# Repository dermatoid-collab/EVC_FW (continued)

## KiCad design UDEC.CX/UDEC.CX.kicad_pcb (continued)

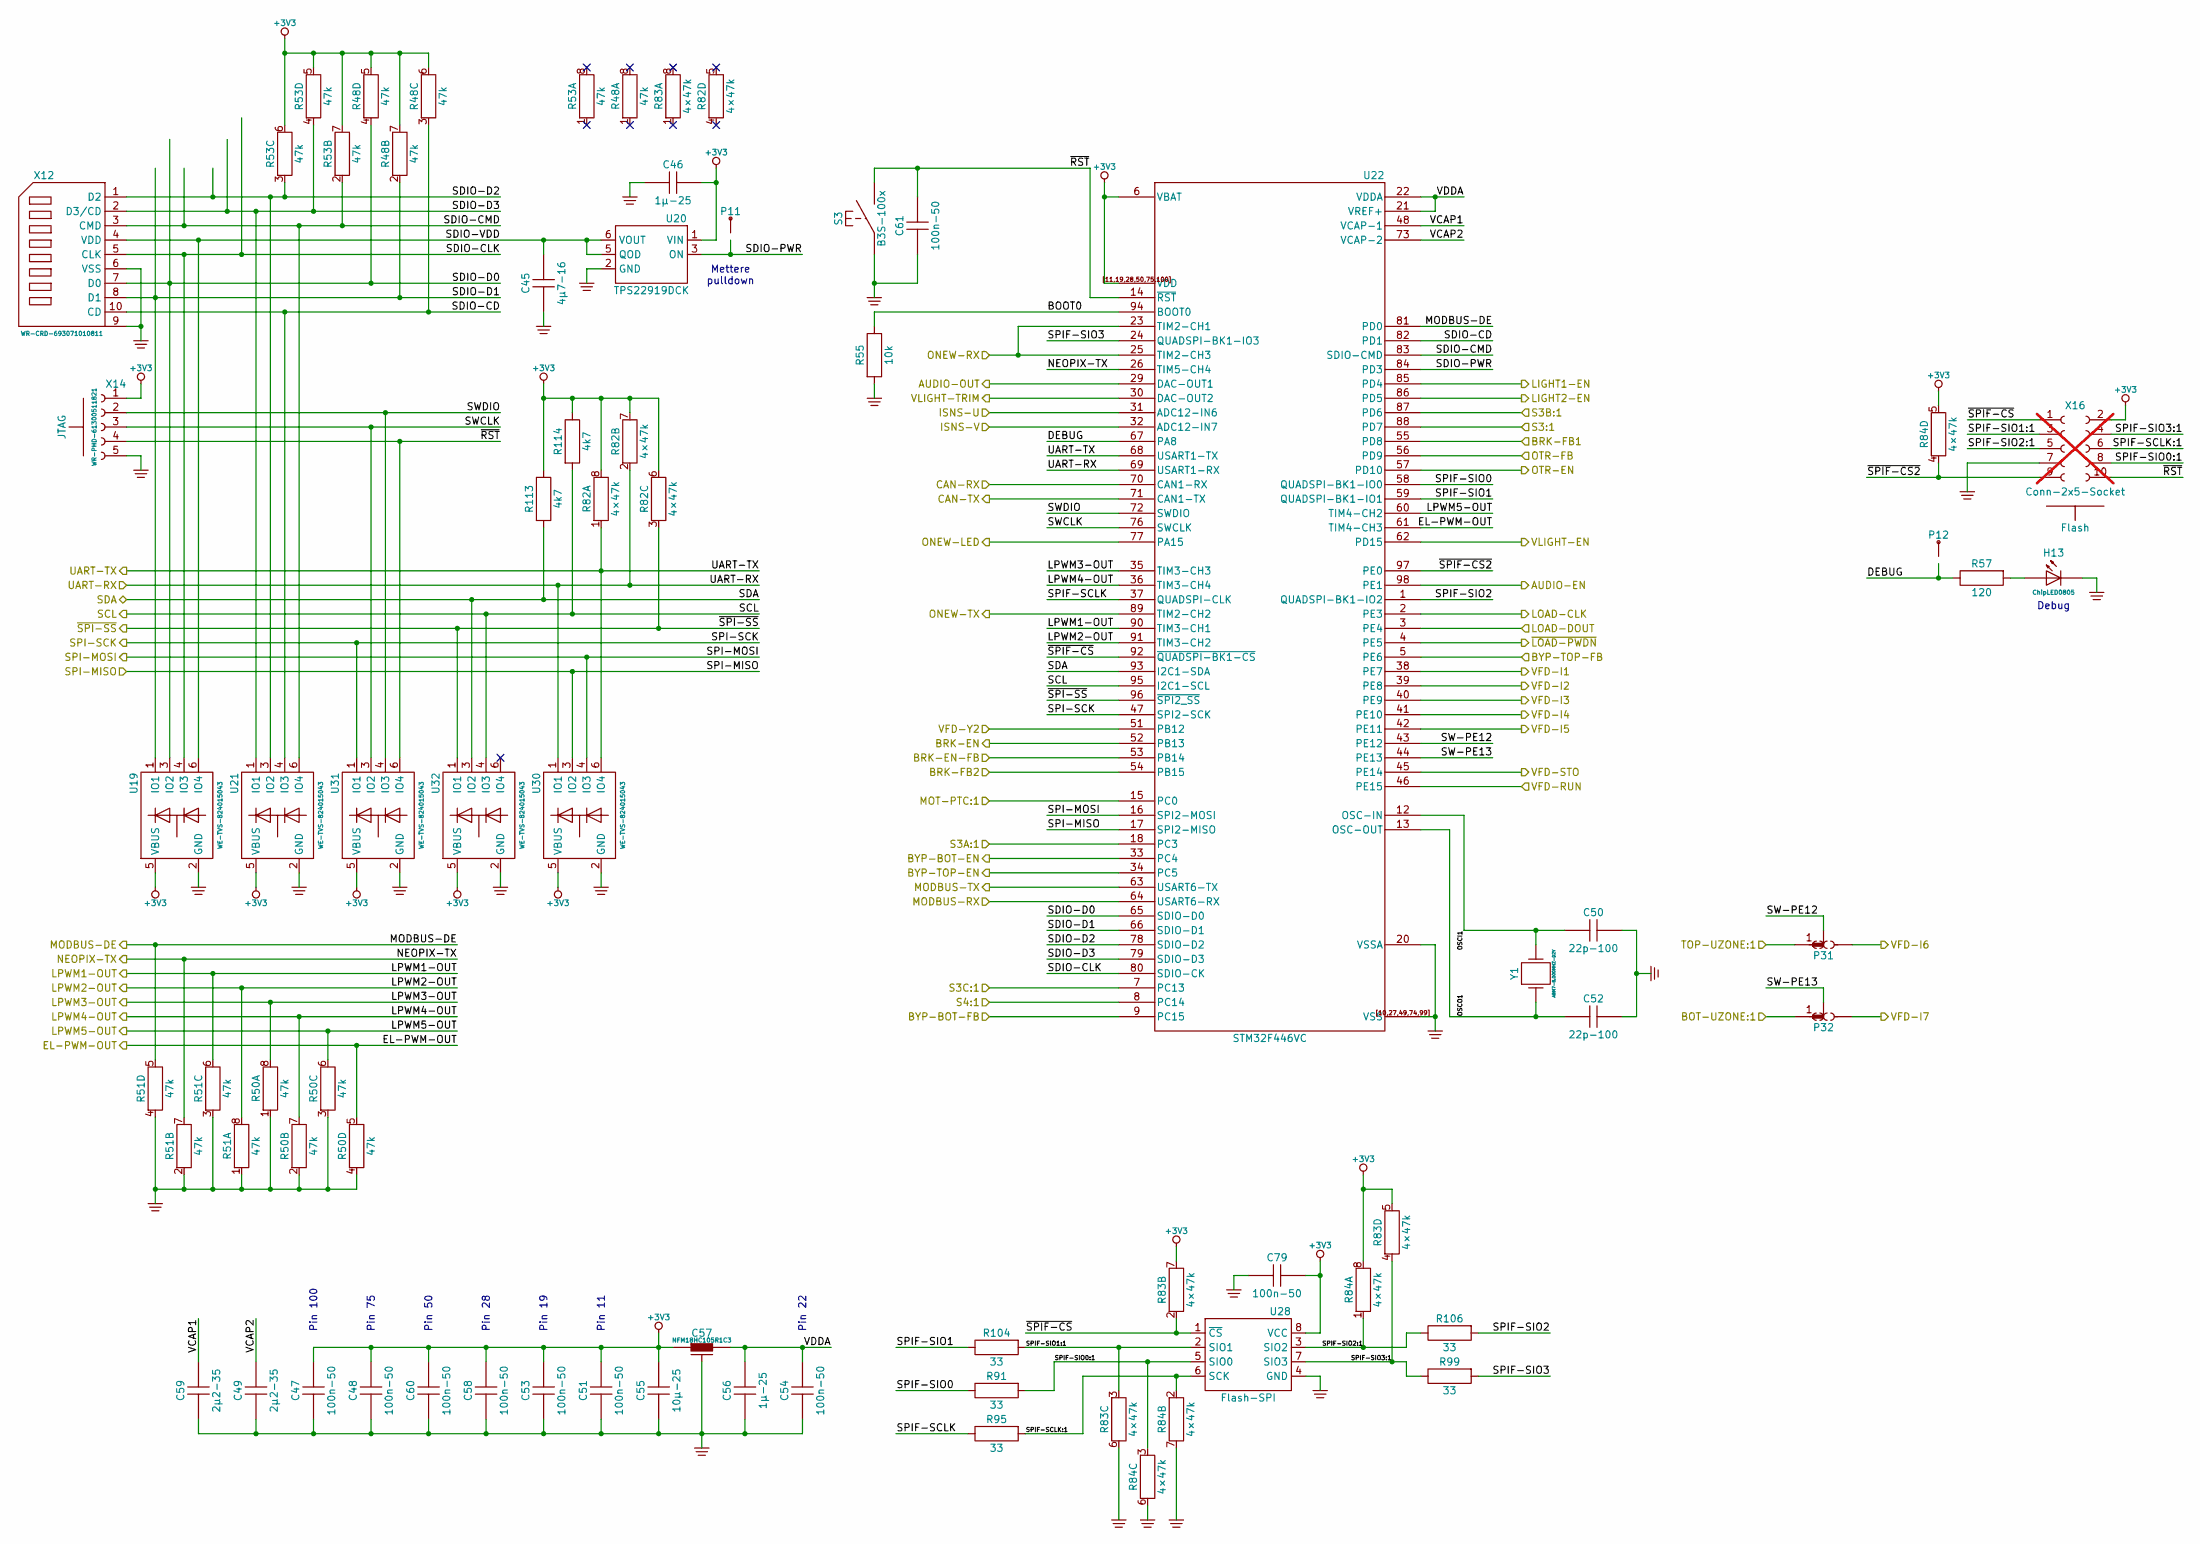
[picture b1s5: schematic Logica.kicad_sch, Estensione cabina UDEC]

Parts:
C45: 4µ7-16; C0603
C46, C56: 1µ-25; C0603
C47, C48, C51, C53, C54, C58, C60, C61, C79: 100n-50; C0603
C49, C59: 2µ2-35; C0603
C50, C52: 22p-100; C0603
C55: 10µ-25; C0805
C57: NFM18HC105R1C3; Murata-NFM18HC105
H13: ChipLED0805; Chipled-0805
P11, P12: PinTst
P31, P32: Solder; Solder-Jumper-CO-Default-03
R48, R50, R51, R53: 47k; KMY-RAC164D
R55: 10k; R0603
R57: 120; R0603
R82, R83, R84: 4×47k; KMY-RAC164D
R91, R95, R99, R104, R106: 33; R0603
R113, R114: 4k7; R0603
S3: B3S-100x; Omron-B3S-100x
U19, U21, U30, U31, U32: WE-TVS-824015043; MO178AB
U20: TPS22919DCK; MO203AB
U22: STM32F446VC; MS026BED
U28: Flash-SPI; MS012AA+208mil
X12: WR-CRD-693071010811
X14: WR-PHD-61300511821; F-5
X16: Conn-2x5-Socket; F-2x5; not fitted
Y1: ABM7-8.000MHZ-D2Y; Abracon-ABM07
ZZZ14: JTAG
ZZZ15: Flash

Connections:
+3V3: C46.2, C47.2, C48.2, C51.2, C53.2, C55.2, C57.1, C58.2, C60.2, C79.2, R48.5, R48.6, R48.7, R53.5, R53.6, R53.7, R82.6, R82.7, R82.8, R83.5, R83.7, R84.5, R84.8, R113.1, R114.1, U19.5 (VBUS), U20.1 (VIN), U21.5 (VBUS), U22.6 (VBAT), U22.11 (VDD), U22.19 (VDD), U22.28 (VDD), U22.50 (VDD), U22.75 (VDD), U22.100 (VDD), U22.[11,19,28,50,75,100] (VDD), U28.8 (VCC), U30.5 (VBUS), U31.5 (VBUS), U32.5 (VBUS), X14.1, X16.2; also elsewhere on the board
/Audio/AUDIO-EN: U22.98 (PE1); also elsewhere on the board
/Audio/AUDIO-OUT: U22.29 (DAC-OUT1); also elsewhere on the board
/Comms/CAN-RX: U22.70 (CAN1-RX); also elsewhere on the board
/Comms/CAN-TX: U22.71 (CAN1-TX); also elsewhere on the board
/Comms/ONEWIRE-LED: U22.77 (PA15); also elsewhere on the board
/Comms/ONEWIRE-RX: U22.23 (TIM2-CH1), U22.25 (TIM2-CH3); also elsewhere on the board
/Comms/ONEWIRE-TX: U22.89 (TIM2-CH2); also elsewhere on the board
/Lighting+EL/BOT-UZONE:1: P32.1 (A); also elsewhere on the board
/Lighting+EL/LIGHT1-EN: U22.85 (PD4); also elsewhere on the board
/Lighting+EL/LIGHT2-EN: U22.86 (PD5); also elsewhere on the board
/Lighting+EL/TOP-UZONE:1: P31.1 (A); also elsewhere on the board
/LoadCell/LOAD-CLK: U22.2 (PE3); also elsewhere on the board
/LoadCell/LOAD-DOUT: U22.3 (PE4); also elsewhere on the board
/LoadCell/~LOAD-PDWN: U22.4 (PE5); also elsewhere on the board
/Logica/BOOT0: R55.1, U22.94 (BOOT0)
/Logica/BRK-EN: U22.52 (PB13); also elsewhere on the board
/Logica/BRK-EN-FB: U22.53 (PB14); also elsewhere on the board
/Logica/BRK-FB1: U22.55 (PD8); also elsewhere on the board
/Logica/BRK-FB2: U22.54 (PB15); also elsewhere on the board
/Logica/BYP-BOT-EN: U22.33 (PC4); also elsewhere on the board
/Logica/BYP-BOT-FB: U22.9 (PC15); also elsewhere on the board
/Logica/BYP-TOP-EN: U22.34 (PC5); also elsewhere on the board
/Logica/BYP-TOP-FB: U22.5 (PE6); also elsewhere on the board
/Logica/DEBUG: P12.1, R57.1, U22.67 (PA8)
/Logica/EL-PWM-OUT: R50.5, U22.61 (TIM4-CH3); also elsewhere on the board
/Logica/ISNS-U: U22.31 (ADC12-IN6); also elsewhere on the board
/Logica/ISNS-V: U22.32 (ADC12-IN7); also elsewhere on the board
/Logica/LPWM1-OUT: R51.6, U22.90 (TIM3-CH1); also elsewhere on the board
/Logica/LPWM2-OUT: R51.8, U22.91 (TIM3-CH2); also elsewhere on the board
/Logica/LPWM3-OUT: R50.8, U22.35 (TIM3-CH3); also elsewhere on the board
/Logica/LPWM4-OUT: R50.7, U22.36 (TIM3-CH4); also elsewhere on the board
/Logica/LPWM5-OUT: R50.6, U22.60 (TIM4-CH2); also elsewhere on the board
/Logica/MODBUS-DE: R51.5, U22.81 (PD0); also elsewhere on the board
/Logica/MODBUS-RX: U22.64 (USART6-RX); also elsewhere on the board
/Logica/MODBUS-TX: U22.63 (USART6-TX); also elsewhere on the board
/Logica/MOT-PTC:1: U22.15 (PC0); also elsewhere on the board
/Logica/NEOPIX-TX: R51.7, U22.26 (TIM5-CH4); also elsewhere on the board
/Logica/OSCI1: C50.2, U22.12 (OSC-IN), Y1.2
/Logica/OSCO1: C52.2, U22.13 (OSC-OUT), Y1.1
/Logica/OTR-EN: U22.57 (PD10); also elsewhere on the board
/Logica/OTR-FB: U22.56 (PD9); also elsewhere on the board
/Logica/S3:1: U22.88 (PD7); also elsewhere on the board
/Logica/S3A:1: U22.18 (PC3); also elsewhere on the board
/Logica/S3B:1: U22.87 (PD6); also elsewhere on the board
/Logica/S3C:1: U22.7 (PC13); also elsewhere on the board
/Logica/S4:1: U22.8 (PC14); also elsewhere on the board
/Logica/SDIO-CD: R48.3, U21.4 (IO3), U22.82 (PD1), X12.10 (CD)
/Logica/SDIO-CLK: U19.4 (IO3), U22.80 (SDIO-CK), X12.5 (CLK)
/Logica/SDIO-CMD: R53.2, U21.6 (IO4), U22.83 (SDIO-CMD), X12.3 (CMD)
/Logica/SDIO-D0: R48.4, U19.3 (IO2), U22.65 (SDIO-D0), X12.7 (D0)
/Logica/SDIO-D1: R48.2, U19.1 (IO1), U22.66 (SDIO-D1), X12.8 (D1)
/Logica/SDIO-D2: R53.3, U21.3 (IO2), U22.78 (SDIO-D2), X12.1 (D2)
/Logica/SDIO-D3: R53.4, U21.1 (IO1), U22.79 (SDIO-D3), X12.2 (D3/CD)
/Logica/SDIO-PWR: P11.1, U20.3 (ON), U22.84 (PD3)
/Logica/SDIO-VDD: C45.2, U19.6 (IO4), U20.5 (QOD), U20.6 (VOUT), X12.4 (VDD)
/Logica/SPIF-SCLK: R95.1, U22.37 (QUADSPI-CLK)
/Logica/SPIF-SCLK:1: R84.2, R95.2, U28.6 (SCK), X16.6
/Logica/SPIF-SIO0: R91.1, U22.58 (QUADSPI-BK1-IO0)
/Logica/SPIF-SIO0:1: R84.3, R91.2, U28.5 (SIO0), X16.8
/Logica/SPIF-SIO1: R104.1, U22.59 (QUADSPI-BK1-IO1)
/Logica/SPIF-SIO1:1: R83.3, R104.2, U28.2 (SIO1), X16.3
/Logica/SPIF-SIO2: R106.2, U22.1 (QUADSPI-BK1-IO2)
/Logica/SPIF-SIO2:1: R84.1, R106.1, U28.3 (SIO2), X16.5
/Logica/SPIF-SIO3: R99.2, U22.24 (QUADSPI-BK1-IO3)
/Logica/SPIF-SIO3:1: R83.4, R99.1, U28.7 (SIO3), X16.4
/Logica/SW-PE12: P31.2 (C), U22.43 (PE12)
/Logica/SW-PE13: P32.2 (C), U22.44 (PE13)
/Logica/SWCLK: U22.76 (SWCLK), U31.3 (IO2), X14.3
/Logica/SWDIO: U22.72 (SWDIO), U31.4 (IO3), X14.2
/Logica/VCAP1: C59.2, U22.48 (VCAP-1)
/Logica/VCAP2: C49.2, U22.73 (VCAP-2)
/Logica/VDDA: C54.2, C56.2, C57.2, U22.21 (VREF+), U22.22 (VDDA)
/Logica/VFD-I1: U22.38 (PE7); also elsewhere on the board
/Logica/VFD-I2: U22.39 (PE8); also elsewhere on the board
/Logica/VFD-I3: U22.40 (PE9); also elsewhere on the board
/Logica/VFD-I4: U22.41 (PE10); also elsewhere on the board
/Logica/VFD-I5: U22.42 (PE11); also elsewhere on the board
/Logica/VFD-I6: P31.3 (B); also elsewhere on the board
/Logica/VFD-I7: P32.3 (B); also elsewhere on the board
/Logica/VFD-RUN: U22.46 (PE15); also elsewhere on the board
/Logica/VFD-STO: U22.45 (PE14); also elsewhere on the board
/Logica/VFD-Y2: U22.51 (PB12); also elsewhere on the board
/Logica/VLIGHT-EN: U22.62 (PD15); also elsewhere on the board
/Logica/VLIGHT-TRIM: U22.30 (DAC-OUT2); also elsewhere on the board
/Logica/~RST: C61.2, S3.14, S3.14A, S3.14B (14A), U22.14 (~RST), U31.6 (IO4), X14.4, X16.10
/Logica/~SPIF-CS2: R84.4, U22.97 (PE0), X16.9
/Logica/~SPIF-CS: R83.2, U22.92 (~QUADSPI-BK1-CS), U28.1 (~CS), X16.1
/SCL: R114.2, U22.95 (I2C1-SCL), U32.4 (IO3); also elsewhere on the board
/SDA: R113.2, U22.93 (I2C1-SDA), U32.3 (IO2); also elsewhere on the board
/SPI-MISO: U22.17 (SPI2-MISO), U30.3 (IO2); also elsewhere on the board
/SPI-MOSI: U22.16 (SPI2-MOSI), U30.4 (IO3); also elsewhere on the board
/SPI-SCK: U22.47 (SPI2-SCK), U31.1 (IO1); also elsewhere on the board
/UART-RX: R82.2, U22.69 (USART1-RX), U30.1 (IO1); also elsewhere on the board
/UART-TX: R82.1, U22.68 (USART1-TX), U30.6 (IO4); also elsewhere on the board
/~SPI-SS: R82.3, U22.96 (~SPI2_SS), U32.1 (IO1); also elsewhere on the board
GND: C45.1, C46.1, C47.1, C48.1, C49.1, C50.1, C51.1, C52.1, C53.1, C54.1, C55.1, C56.1, C57.3, C58.1, C59.1, C60.1, C61.1, C79.1, H13.K, R50.1, R50.2, R50.3, R50.4, R51.1, R51.2, R51.3, R51.4, R55.2, R83.6, R84.6, R84.7, S3.13, S3.13A, S3.13B, U19.2 (GND), U20.2 (GND), U21.2 (GND), U22.10 (VSS), U22.20 (VSSA), U22.27 (VSS), U22.49 (VSS), U22.74 (VSS), U22.99 (VSS), U22.[10,27,49,74,99] (VSS), U28.4 (GND), U30.2 (GND), U31.2 (GND), U32.2 (GND), X12.6 (VSS), X12.9, X14.5, X16.7; also elsewhere on the board
unnamed: H13.A, R57.2

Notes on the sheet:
Pin 50
Pin 28
Pin 19
Pin 22
Mettere pulldown
Debug
Pin 100
Pin 11
Pin 75

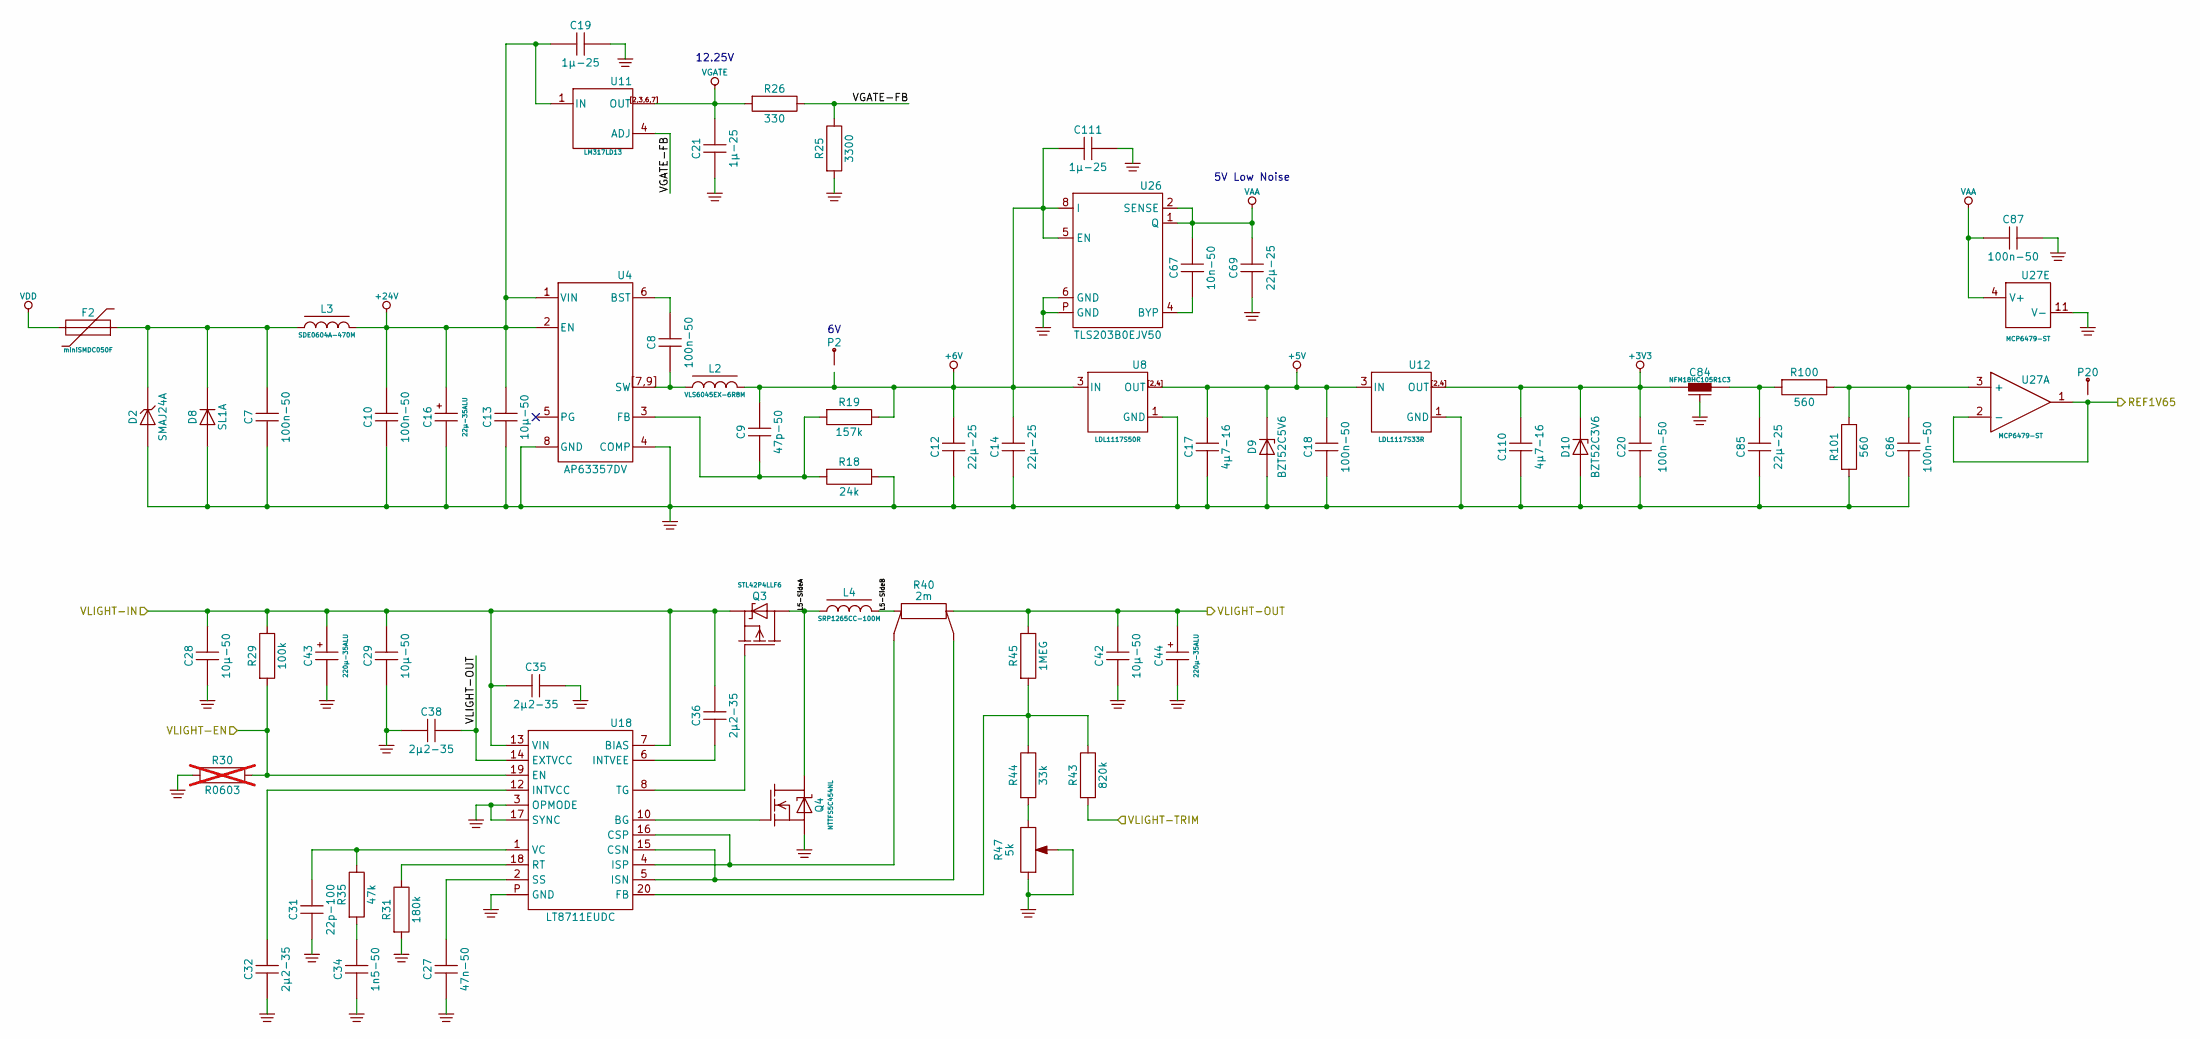
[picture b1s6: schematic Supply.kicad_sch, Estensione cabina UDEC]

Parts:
C7, C8, C10, C18, C20, C86, C87: 100n-50; C0603
C9: 47p-50; C0603
C12, C14, C69, C85: 22µ-25; C0805
C13, C28, C29, C42: 10µ-50; C1206
C16: 22µ-35ALU; CPV-5x5.5
C17, C110: 4µ7-16; C0603
C19, C21, C111: 1µ-25; C0603
C27: 47n-50; C0603
C31: 22p-100; C0603
C32, C35, C36, C38: 2µ2-35; C0603
C34: 1n5-50; C0603
C43, C44: 220µ-35ALU; CPV-8x10.5
C67: 10n-50; C0603
C84: NFM18HC105R1C3; Murata-NFM18HC105
D2: SMAJ24A; DO214AC
D8: SL1A; SOD123FL
D9: BZT52C5V6; SOD123
D10: BZT52C3V6; SOD123
F2: miniSMDC050F; miniSMDC
L2: VLS6045EX-6R8M; TDK-VLS6045EX
L3: SDE0604A-470M; Bourns-SDE0604A
L4: SRP1265CC-100M; Bourns-SRP1265CC
P2, P20: PinTst
Q3: STL42P4LLF6; ST-PowerFlat-5x6-R-SUBCON-SSSGDDDD
Q4: NTTFS5C454NL; Onsemi-WDFN8-511AB
R18: 24k; R0603
R19: 157k; R0603
R25: 3300; R0603
R26: 330; R0603
R29: 100k; R0603
R30: R0603; not fitted
R31: 180k; R0603
R35: 47k; R0603
R40: 2m; R2512K
R43: 820k; R0603
R44: 33k; R0603
R45: 1MEG; R0603
R47: 5k; Vishay-T73YP
R100, R101: 560; R0603
U4: AP63357DV; Diodes-V-DFN3020-13A
U8: LDL1117S50R; TO261AA
U11: LM317LD13; MS012AA
U12: LDL1117S33R; TO261AA
U18: LT8711EUDC; Linear-UDC20
U26: TLS203B0EJV50; MS012BA
U27: MCP6479-ST; MO153AB1

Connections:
+3V3: C20.2, C84.1, C110.2, D10.K, U12.2 (OUT), U12.4 (OUT), U12.[2,4] (OUT); also elsewhere on the board
+5V: C17.2, C18.2, D9.K, U8.2 (OUT), U8.4 (OUT), U8.[2,4] (OUT), U12.3 (IN); also elsewhere on the board
+6V: C9.2, C12.2, C14.2, C111.2, L2.2, P2.1, R19.1, U8.3 (IN), U26.5 (EN), U26.8 (I); also elsewhere on the board
+24V: C10.2, C13.2, C16.+, C19.1, L3.2, U4.1 (VIN), U4.2 (EN), U11.1 (IN); also elsewhere on the board
/Logica/VLIGHT-EN: R29.2, R30.1, U18.19 (EN); also elsewhere on the board
/Logica/VLIGHT-TRIM: R43.2; also elsewhere on the board
/REF1V65: P20.1, U27.1, U27.2 (-); also elsewhere on the board
/Supply/L5-SideA: L4.1, Q3.D, Q4.D
/Supply/L5-SideB: L4.2, R40.2
/Supply/VGATE-FB: R25.1, R26.1, U11.4 (ADJ)
/VLIGHT-IN: C28.2, C29.2, C35.1, C36.2, C43.+, Q3.S, R29.1, U18.7 (BIAS), U18.13 (VIN); also elsewhere on the board
/VLIGHT-OUT: C38.2, C42.2, C44.+, R40.1, R45.1, U18.14 (EXTVCC); also elsewhere on the board
GND: C7.1, C10.1, C12.1, C13.1, C14.1, C16.-, C17.1, C18.1, C19.2, C20.1, C21.1, C27.1, C28.1, C29.1, C31.1, C32.1, C34.1, C35.2, C38.1, C42.1, C43.-, C44.-, C69.1, C84.3, C85.1, C86.1, C87.2, C110.1, C111.1, D2.A, D8.A, D9.A, D10.A, Q4.S, R18.1, R25.2, R30.2, R31.2, R47.3, R47.W, R101.2, U4.4 (COMP), U4.8 (GND), U8.1 (GND), U12.1 (GND), U18.3 (OPMODE), U18.17 (SYNC), U18.P (GND), U26.6 (GND), U26.P (GND), U27.11 (V-); also elsewhere on the board
unnamed: C7.2, D2.K, D8.K, F2.2, L3.1
unnamed: C34.2, R35.2
unnamed: C84.2, C85.2, R100.2
unnamed: R44.2, R47.1
unnamed: C8.2, U4.6 (BST)
unnamed: C9.1, R18.2, R19.2, U4.3 (FB)
unnamed: C8.1, L2.1, U4.7 (SW), U4.9 (SW), U4.[7,9] (SW)
unnamed: Q4.G, U18.10 (BG)
unnamed: R40.3, U18.5 (ISN), U18.15 (CSN)
unnamed: R40.4, U18.4 (ISP), U18.16 (CSP)
unnamed: R43.1, R44.1, R45.2, U18.20 (FB)
unnamed: C32.2, U18.12 (INTVCC)
unnamed: C36.1, U18.6 (INTVEE)
unnamed: R31.1, U18.18 (RT)
unnamed: C27.2, U18.2 (SS)
unnamed: Q3.G, U18.8 (TG)
unnamed: C31.2, R35.1, U18.1 (VC)
unnamed: C67.1, U26.4 (BYP)
unnamed: C86.2, R100.1, R101.1, U27.3 (+)
VAA: C67.2, C69.2, C87.1, U26.1 (Q), U26.2 (SENSE), U27.4 (V+); also elsewhere on the board
VDD: F2.1; also elsewhere on the board
VGATE: C21.2, R26.2, U11.2 (OUT), U11.3 (OUT), U11.6 (OUT), U11.7 (OUT), U11.[2,3,6,7] (OUT); also elsewhere on the board

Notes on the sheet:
5V Low Noise
12.25V

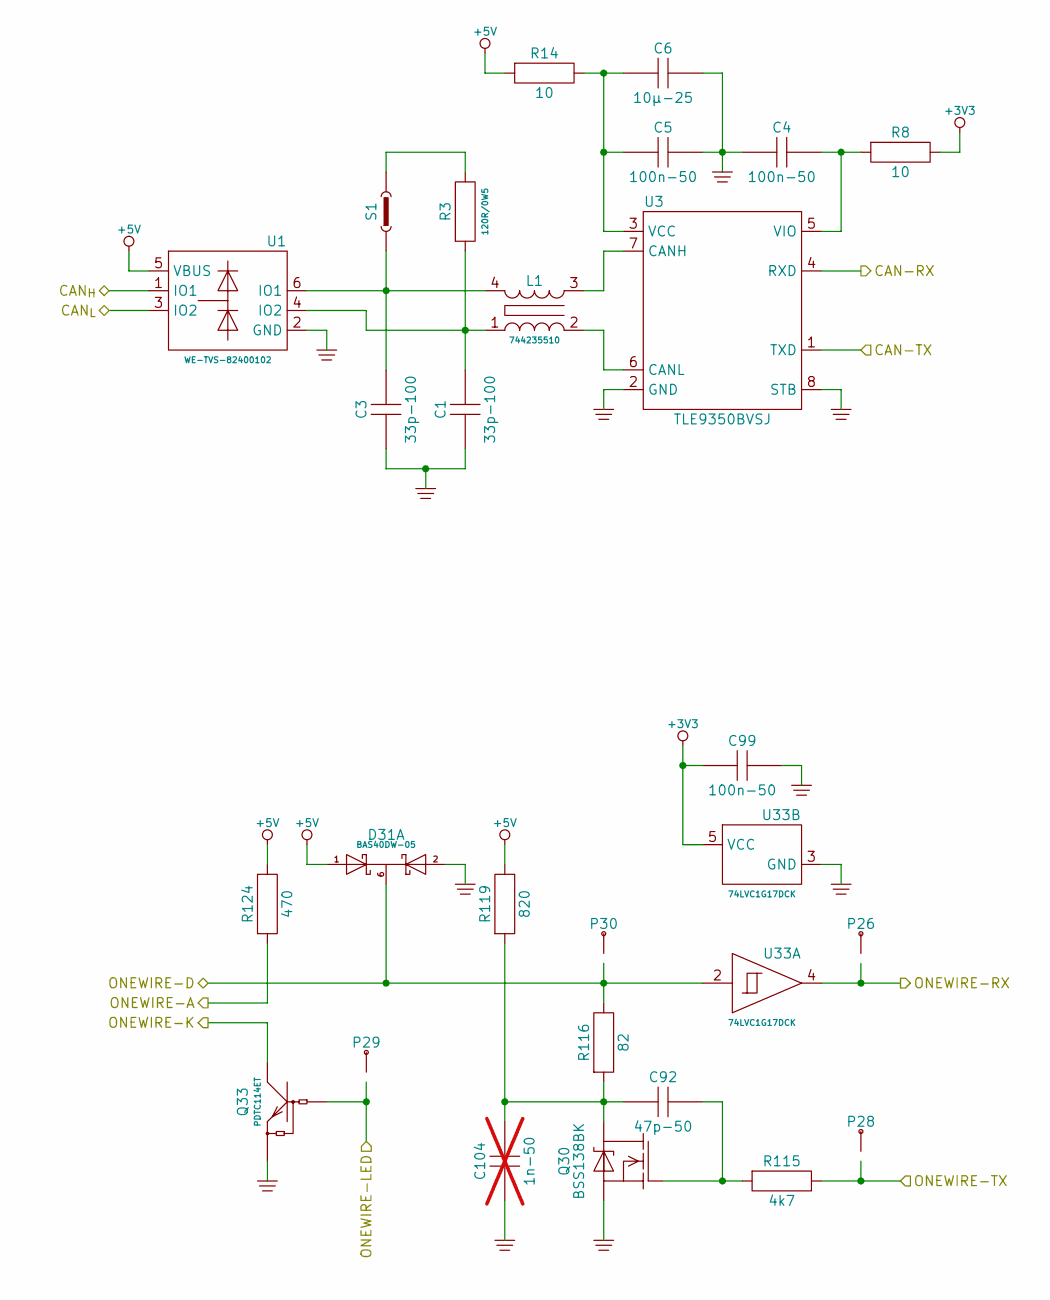
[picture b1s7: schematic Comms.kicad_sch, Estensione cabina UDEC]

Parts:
C1, C3: 33p-100; C0603
C4, C5, C99: 100n-50; C0603
C6: 10µ-25; C0805
C92: 47p-50; C0603
C104: 1n-50; C0603; not fitted
D31: BAS40DW-05; MO203AB
L1: 744235510; WE-CNSW-1812
P26, P28, P29, P30: PinTst
Q30: BSS138BK; TO236-GSD
Q33: PDTC114ET; TO236-BEC
R3: 120R/0W5; R1210
R8, R14: 10; R0603
R115: 4k7; R0603
R116: 82; R0603
R119: 820; R0603
R124: 470; R0603
S1: Jumper-2.54
U1: WE-TVS-82400102; MO178AB
U3: TLE9350BVSJ; MS012AA
U33: 74LVC1G17DCK; MO203AA

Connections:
+3V3: C99.2, R8.1, U33.5 (VCC); also elsewhere on the board
+5V: D31.1 (A1), R14.2, R119.1, R124.1, U1.5 (VBUS); also elsewhere on the board
/CAN_{H}: U1.1 (IO1); also elsewhere on the board
/CAN_{L}: U1.3 (IO2); also elsewhere on the board
/Comms/CAN-RX: U3.4 (RXD); also elsewhere on the board
/Comms/CAN-TX: U3.1 (TXD); also elsewhere on the board
/Comms/ONEWIRE-LED: P29.1, Q33.B; also elsewhere on the board
/Comms/ONEWIRE-RX: P26.1, U33.4; also elsewhere on the board
/Comms/ONEWIRE-TX: P28.1, R115.1; also elsewhere on the board
/ONEWIRE-A: R124.2; also elsewhere on the board
/ONEWIRE-D: D31.6 (K), P30.1, R116.1, U33.2; also elsewhere on the board
/ONEWIRE-K: Q33.C; also elsewhere on the board
GND: C1.1, C3.1, C4.2, C5.1, C6.2, C99.1, C104.1, D31.2 (A2), Q30.S, Q33.E, U1.2 (GND), U3.2 (GND), U3.8 (STB), U33.3 (GND); also elsewhere on the board
unnamed: C1.2, L1.1, R3.2, U1.4 (IO2)
unnamed: C3.2, L1.4, S1.1, U1.6 (IO1)
unnamed: C92.2, Q30.G, R115.2
unnamed: C92.1, C104.2, Q30.D, R116.2, R119.2
unnamed: R3.1, S1.2
unnamed: L1.3, U3.7 (CANH)
unnamed: L1.2, U3.6 (CANL)
unnamed: C5.2, C6.1, R14.1, U3.3 (VCC)
unnamed: C4.1, R8.2, U3.5 (VIO)

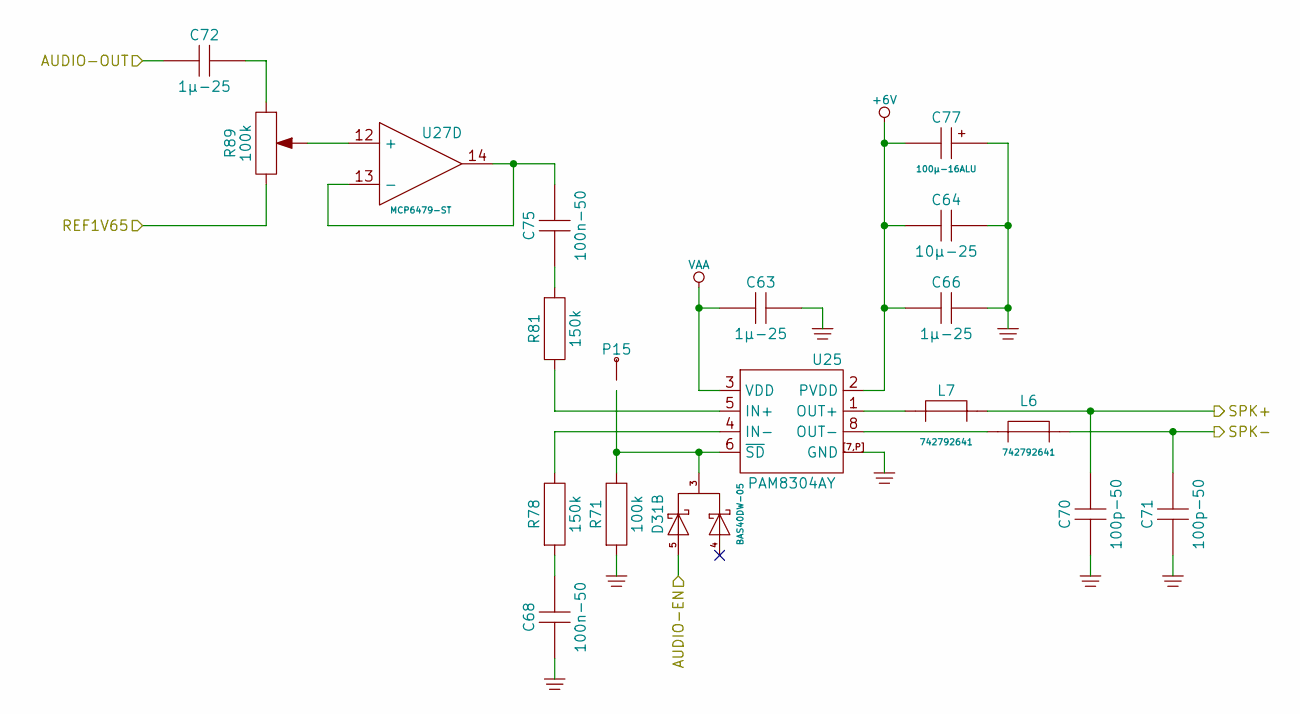
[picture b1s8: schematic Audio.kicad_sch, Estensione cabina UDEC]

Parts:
C63, C66, C72: 1µ-25; C0603
C64: 10µ-25; C0805
C68, C75: 100n-50; C0603
C70, C71: 100p-50; C0603
C77: 100µ-16ALU; CPV-6.3x5.5
D31: BAS40DW-05; MO203AB
L6, L7: 742792641; WE-CBF-0603-HC
P15: PinTst
R71: 100k; R0603
R78, R81: 150k; R0603
R89: 100k; Vishay-T73YP
U25: PAM8304AY; Diodes-U-DFN3030-8-E
U27: MCP6479-ST; MO153AB1

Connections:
+6V: C64.1, C66.1, C77.-, U25.2 (PVDD); also elsewhere on the board
/Audio/AUDIO-EN: D31.5 (A2); also elsewhere on the board
/Audio/AUDIO-OUT: C72.1; also elsewhere on the board
/REF1V65: R89.1; also elsewhere on the board
/SPK+: C70.2, L7.2; also elsewhere on the board
/SPK-: C71.2, L6.2; also elsewhere on the board
GND: C63.2, C64.2, C66.2, C68.1, C70.1, C71.1, C77.+, R71.2, U25.7 (GND), U25.P (GND), U25.[7,P] (GND); also elsewhere on the board
unnamed: C68.2, R78.2
unnamed: C72.2, R89.3
unnamed: C75.2, R81.2
unnamed: D31.3 (K), P15.1, R71.1, U25.6 (~SD)
unnamed: R81.1, U25.5 (IN+)
unnamed: R78.1, U25.4 (IN-)
unnamed: L7.1, U25.1 (OUT+)
unnamed: L6.1, U25.8 (OUT-)
unnamed: R89.W, U27.12 (+)
unnamed: C75.1, U27.13 (-), U27.14
VAA: C63.1, U25.3 (VDD); also elsewhere on the board

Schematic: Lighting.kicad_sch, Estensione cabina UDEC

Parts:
C2, C39, C40, C41: 100n-50; C0603
C24, C25, C26: 1µ-25; C0603
C107, C108: 10n-50; C0603
C109: 1µ-50; C1206
D11: BAS40DW-06; MO203AB
D12: BAS40DW-05; MO203AB
D14, D15, D16, D17, D18: SMAJ24A; DO214AC; not fitted
D19, D32, D37: SMAJ24A; DO214AC
D33, D34: MBRS240; DO214AA
H14, H21, H27, H28: ChipLED0805; Chipled-0805
K6, K7: G5LE-1DC24; Omron-G5LE-1
P24, P25: PinTst
Q5, Q6, Q7, Q8, Q9, Q10: NTTFS5C454NL; Onsemi-WDFN8-511AB
Q31: NUD3160D; MO193AA
R42: 330; R0603
R46, R49, R52, R54, R56, R58: 4R7; R0603
R73, R107: 3.3k/0W25; R1206
R127, R128: WE-VS-82550250; WE-VS-0805
R129, R130: 1k8 250mW; R1206
R131, R132: 270; R0603
R133: 68k; R0603
R134: 1k5; R0603
U2: 74AHCT1G125GV; MO178AA
U15, U16, U17: 2EDN7534BXTSA1; MO178AB
U34: MAX15162ATG; MO220WGGD2

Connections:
+3V3: D12.3 (K), U34.1 (EN2), U34.24 (EN1); also elsewhere on the board
+5V: C2.1, U2.5 (VCC); also elsewhere on the board
+24V: K6.A1, K7.A1, R73.1, R107.1; also elsewhere on the board
/BOT-UZONE: D33.A, R128.2, R130.2; also elsewhere on the board
/EL_{M}: D19.K, Q10.D; also elsewhere on the board
/EL_{P}: D32.K, U34.11 (OUT2), U34.12 (OUT2), U34.19 (OUT1), U34.20 (OUT1), U34.[11,12] (OUT2), U34.[19,20] (OUT1); also elsewhere on the board
/LIGHT1-IN: K7.14; also elsewhere on the board
/LIGHT1-OUT: K7.11; also elsewhere on the board
/LIGHT2-IN: K6.14; also elsewhere on the board
/LIGHT2-OUT: K6.11; also elsewhere on the board
/LPWM1-OUT: D14.K, Q5.D; also elsewhere on the board
/LPWM2-OUT: D16.K, Q7.D; also elsewhere on the board
/LPWM3-OUT: D18.K, Q9.D; also elsewhere on the board
/LPWM4-OUT: D15.K, Q6.D; also elsewhere on the board
/LPWM5-OUT: D17.K, Q8.D; also elsewhere on the board
/Lighting+EL/BOT-UZONE:1: C108.2, D12.4 (A1), H28.K, R132.1; also elsewhere on the board
/Lighting+EL/LIGHT1-EN: P24.1, Q31.2 (G); also elsewhere on the board
/Lighting+EL/LIGHT2-EN: P25.1, Q31.5 (G); also elsewhere on the board
/Lighting+EL/TOP-UZONE:1: C107.2, D12.5 (A2), H27.K, R131.1; also elsewhere on the board
/Logica/EL-PWM-OUT: U17.5 (INB); also elsewhere on the board
/Logica/LPWM1-OUT: U15.4 (INA); also elsewhere on the board
/Logica/LPWM2-OUT: U15.5 (INB); also elsewhere on the board
/Logica/LPWM3-OUT: U16.4 (INA); also elsewhere on the board
/Logica/LPWM4-OUT: U16.5 (INB); also elsewhere on the board
/Logica/LPWM5-OUT: U17.4 (INA); also elsewhere on the board
/Logica/NEOPIX-TX: U2.2; also elsewhere on the board
/NEOPIX-OUT: R42.1; also elsewhere on the board
/TOP-UZONE: D34.A, R127.2, R129.2; also elsewhere on the board
GND: C2.2, C24.1, C25.1, C26.1, C39.1, C40.1, C41.1, C107.1, C108.1, C109.1, D11.3 (A), D14.A, D15.A, D16.A, D17.A, D18.A, D19.A, D32.A, D37.A, H14.K, H21.K, Q5.S, Q6.S, Q7.S, Q8.S, Q9.S, Q10.S, Q31.1 (4), Q31.4, R127.1, R128.1, R131.2, R132.2, R133.2, R134.2, U2.1 (~OE), U2.3 (GND), U15.2 (GND), U16.2 (GND), U17.2 (GND), U34.4 (GND), U34.P (GND), U34.[4,P] (GND); also elsewhere on the board
unnamed: D11.4 (K1), H28.A, R130.1
unnamed: D11.5 (K2), H27.A, R129.1
unnamed: H14.A, R73.2
unnamed: H21.A, R107.2
unnamed: Q5.G, R46.1
unnamed: Q6.G, R49.1
unnamed: Q7.G, R52.1
unnamed: Q8.G, R54.1
unnamed: Q9.G, R56.1
unnamed: Q10.G, R58.1
unnamed: K7.A2, Q31.6 (D)
unnamed: K6.A2, Q31.3 (D)
unnamed: R42.2, U2.4
unnamed: R46.2, U15.3 (OUTA)
unnamed: R52.2, U15.1 (OUTB)
unnamed: R56.2, U16.3 (OUTA)
unnamed: R49.2, U16.1 (OUTB)
unnamed: R54.2, U17.3 (OUTA)
unnamed: R58.2, U17.1 (OUTB)
unnamed: R133.1, U34.2 (DLY)
unnamed: R134.1, U34.3 (IMON1), U34.5 (IMON2)
unnamed: C109.2, D33.K, D34.K, D37.K, U34.15 (IN), U34.16 (IN), U34.[15,16] (IN)
VGATE: C24.2, C25.2, C26.2, C39.2, C40.2, C41.2, U15.6 (VDD), U16.6 (VDD), U17.6 (VDD); also elsewhere on the board

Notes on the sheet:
Light Bank 1
Zona sblocco inferiore
Light Bank 2
Zona sblocco superiore

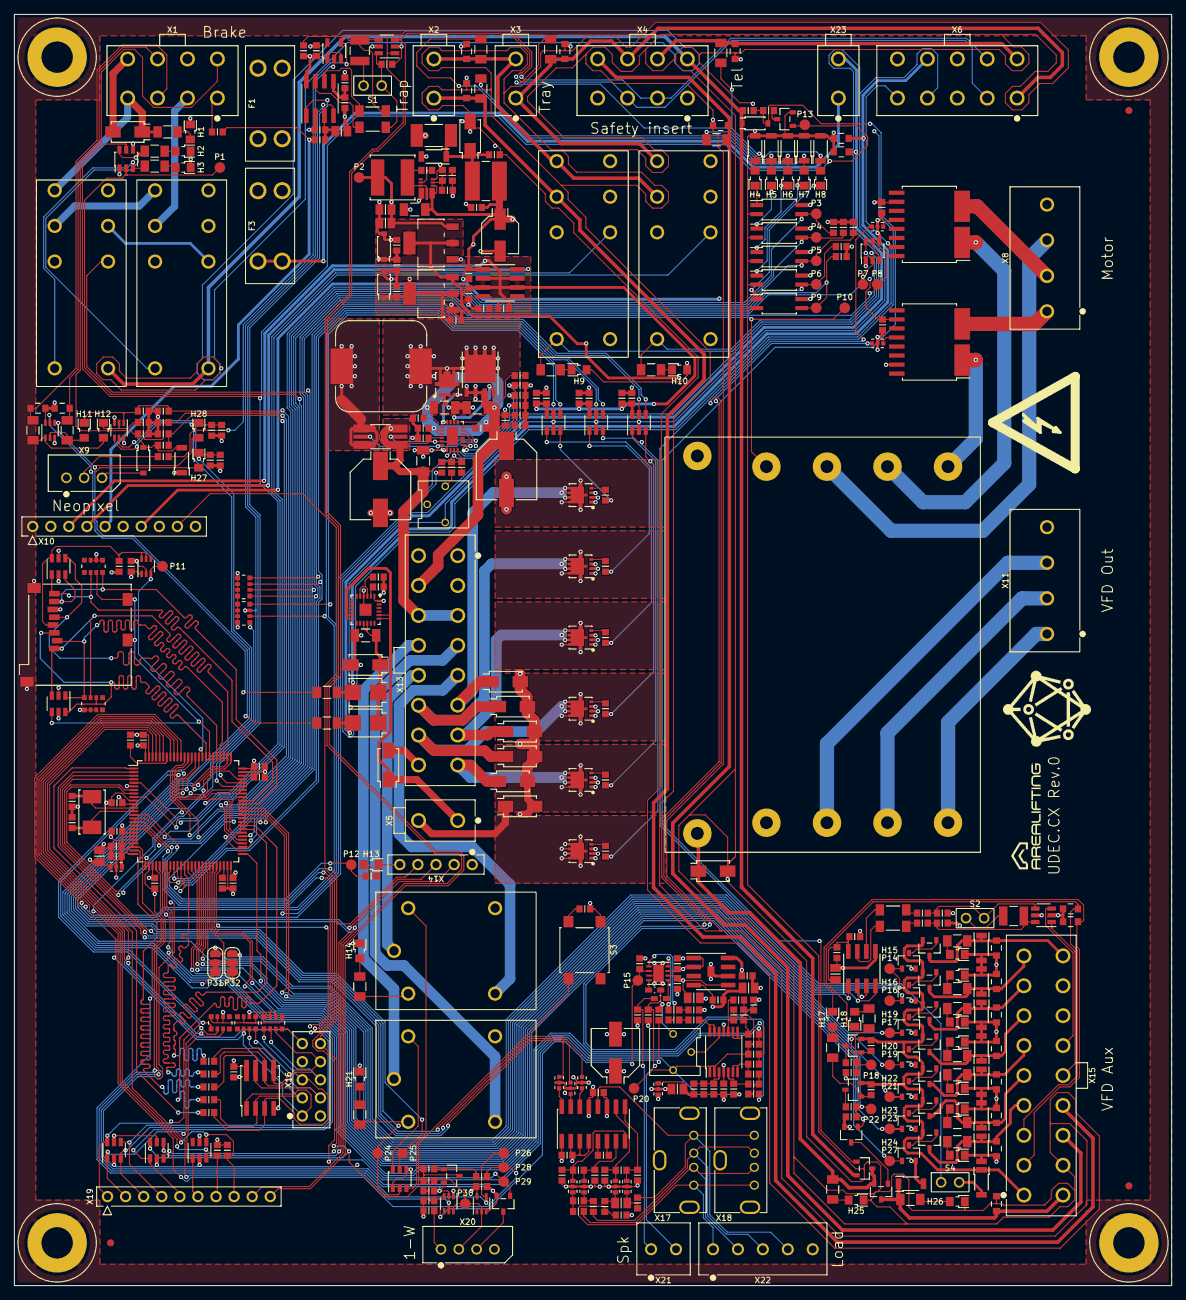
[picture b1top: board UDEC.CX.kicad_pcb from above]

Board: 4 copper layers, 162.5 x 178.5 mm, 464 parts (0 on the bottom side), 311 nets.
